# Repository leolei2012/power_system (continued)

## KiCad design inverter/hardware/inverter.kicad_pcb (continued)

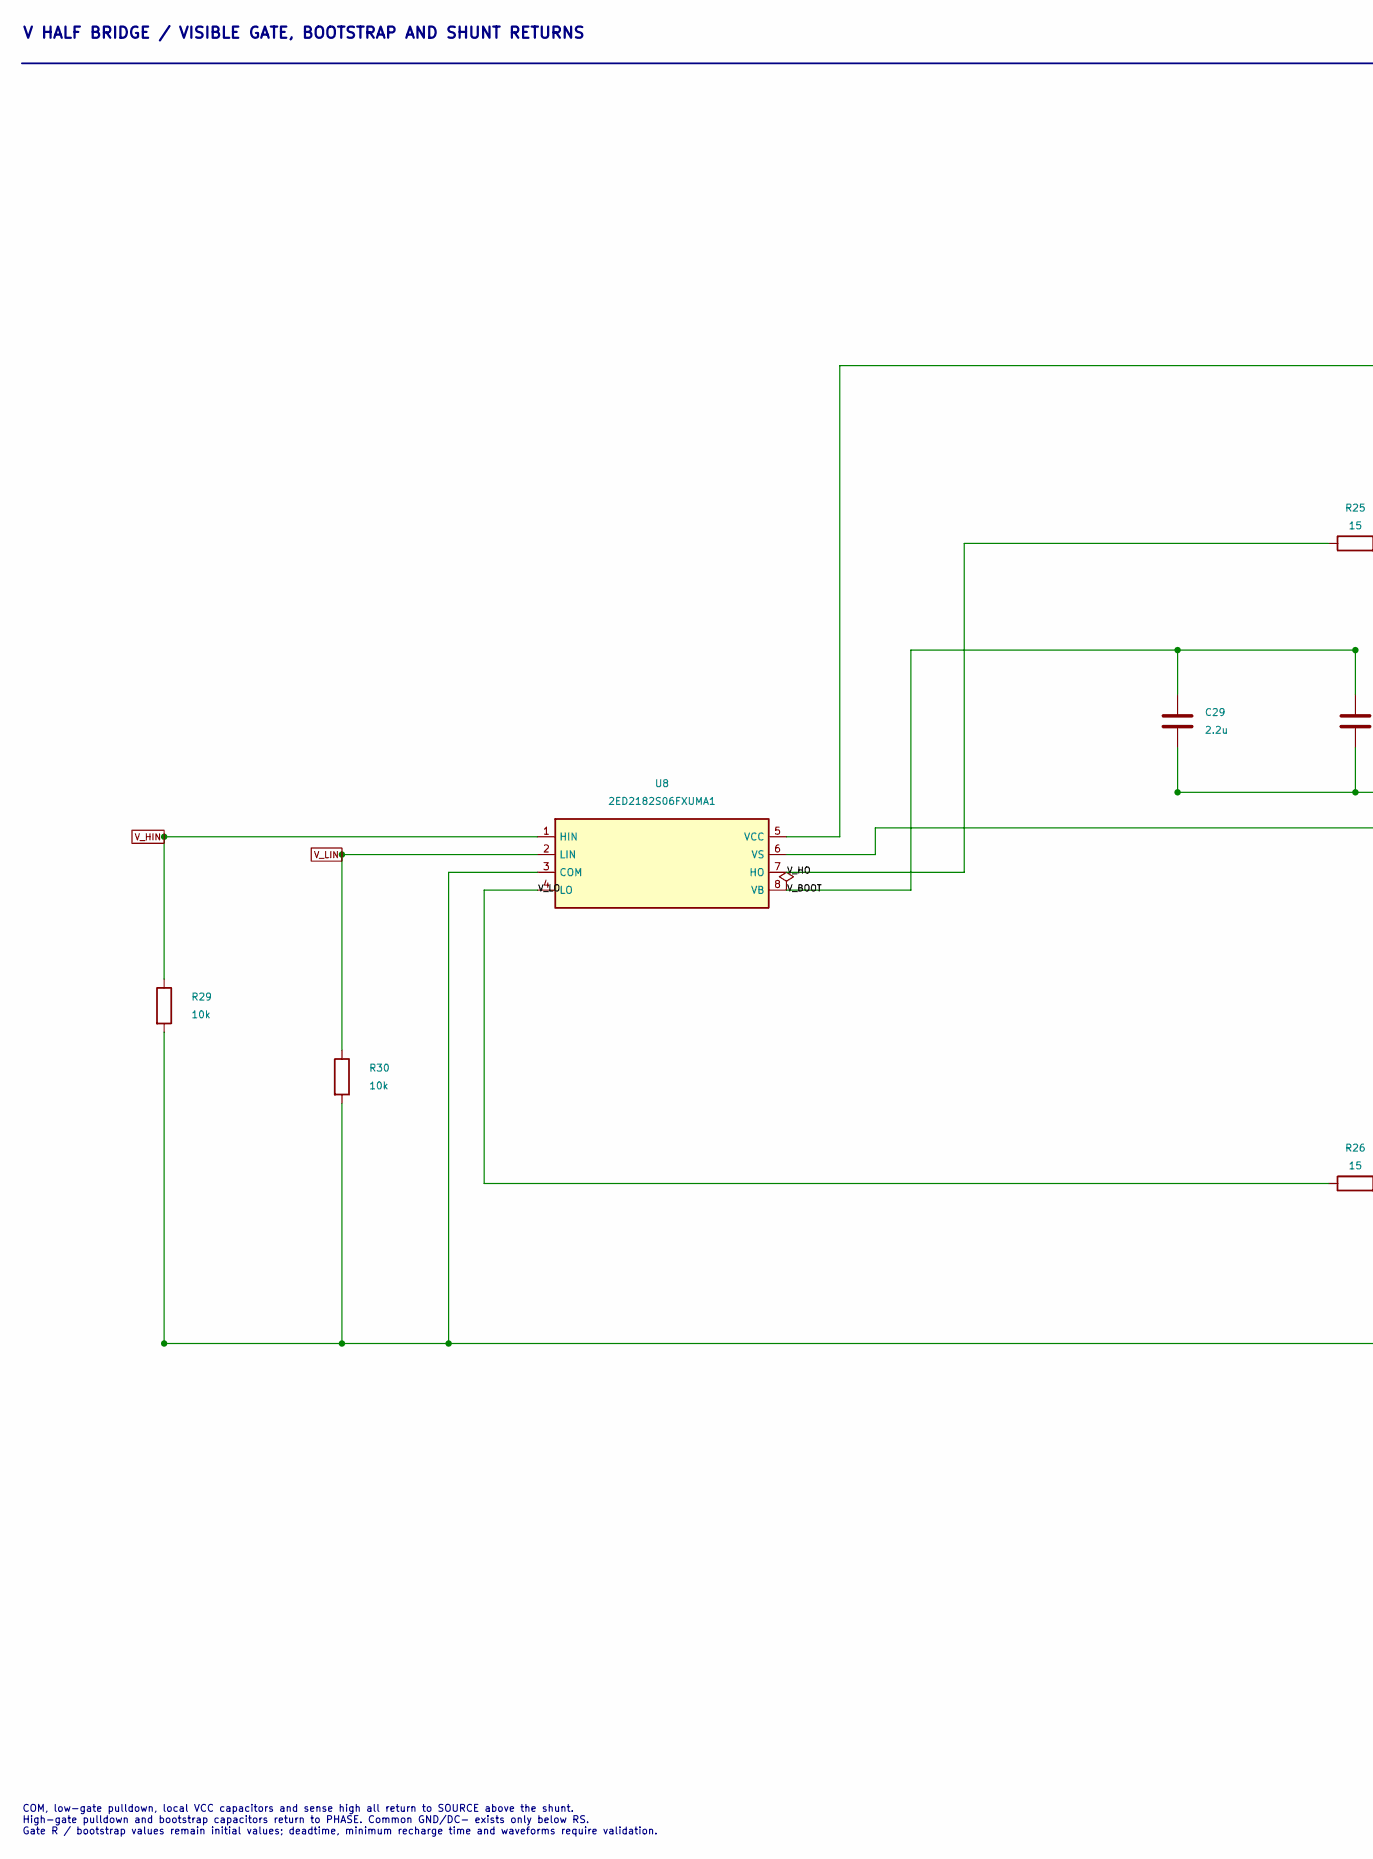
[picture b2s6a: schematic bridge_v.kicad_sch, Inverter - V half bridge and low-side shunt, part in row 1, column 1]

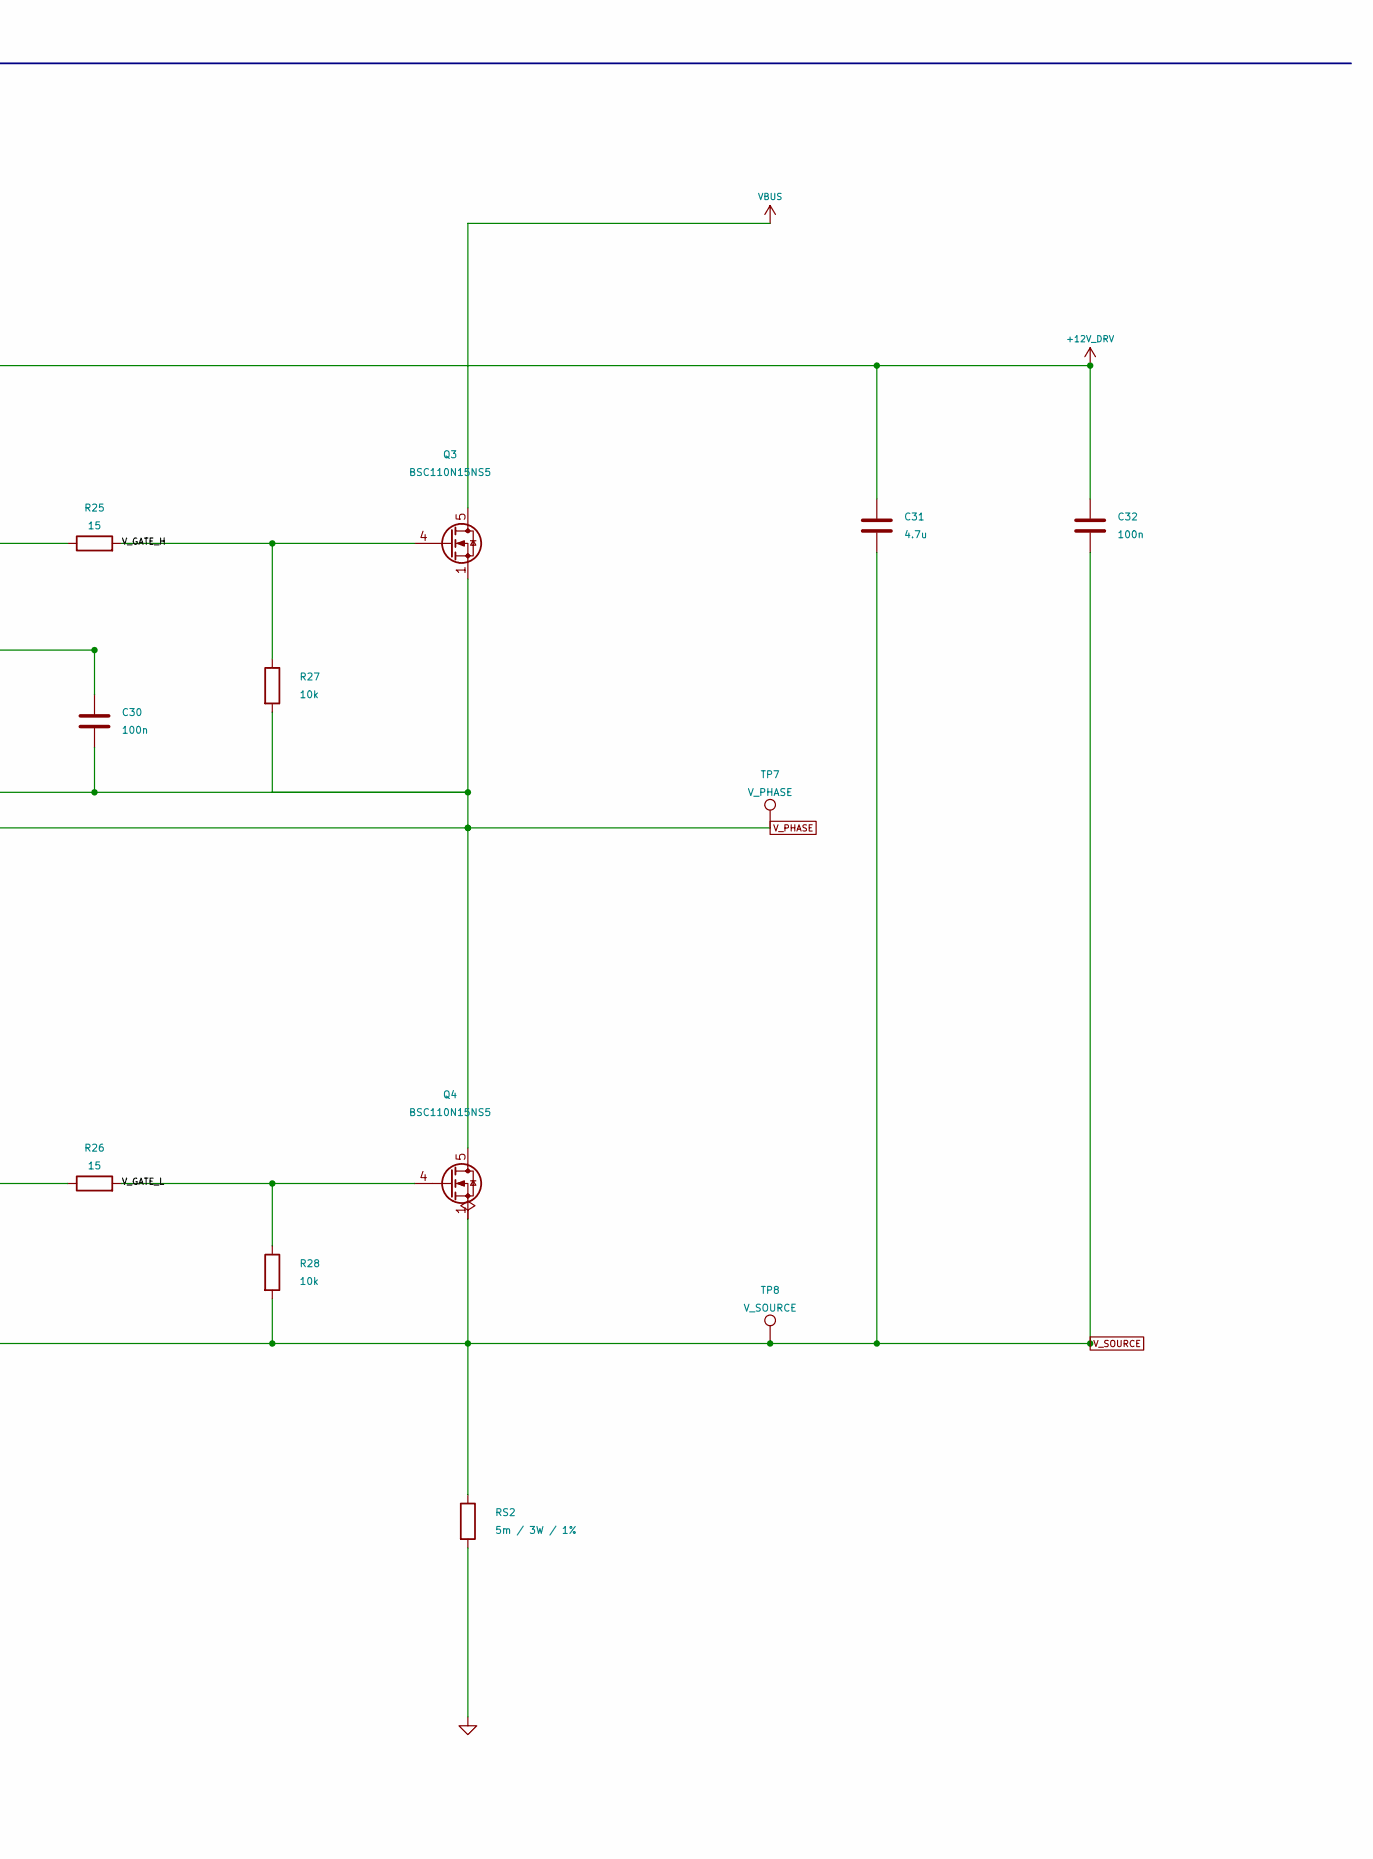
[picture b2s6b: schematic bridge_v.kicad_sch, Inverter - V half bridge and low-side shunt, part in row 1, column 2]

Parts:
C29: 2.2u; C_1206_3216Metric; Voltage_Rating 25V; MPN TBD
C30, C32: 100n; C_0603_1608Metric; Voltage_Rating 50V; Tolerance 10%; MPN CC0603KRX7R9BB104
C31: 4.7u; C_0805_2012Metric; Voltage_Rating 25V; MPN TBD
Q3, Q4: BSC110N15NS5; Infineon_BSC110N15NS5_PG-TDSON8_8PhysicalPins; MPN BSC110N15NS5ATMA1
R25, R26: 15; R_0805_2012Metric; Tolerance 1%; MPN TBD
R27, R28, R29, R30: 10k; R_0603_1608Metric; Tolerance 1%; MPN TBD
RS2: 5m / 3W / 1%; Milliohm_HoJLR2512_Pad2.1x4.0mm_Gap4.1mm; MPN HoJLR2512-3W-5mR-1%
TP7: V_PHASE; TestPoint_Pad_D1.5mm
TP8: V_SOURCE; TestPoint_Pad_D1.5mm
U8: 2ED2182S06FXUMA1; SOIC-8_3.9x4.9mm_P1.27mm; MPN 2ED2182S06FXUMA1

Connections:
+12V_DRV: C31.1, C32.1, U8.5 (VCC); also elsewhere on the board
/V half bridge/V_BOOT: C29.1, C30.1, U8.8 (VB)
/V half bridge/V_GATE_H: Q3.4 (G), R25.2, R27.1
/V half bridge/V_GATE_L: Q4.4 (G), R26.2, R28.1
/V half bridge/V_HO: R25.1, U8.7 (HO)
/V half bridge/V_LO: R26.1, U8.4 (LO)
VBUS: Q3.5 (D), Q3.6 (D), Q3.7 (D), Q3.8 (D); also elsewhere on the board
V_HIN: R29.1, U8.1 (HIN); also elsewhere on the board
V_LIN: R30.1, U8.2 (LIN); also elsewhere on the board
V_PHASE: C29.2, C30.2, Q3.1 (S), Q3.2 (S), Q3.3 (S), Q4.5 (D), Q4.6 (D), Q4.7 (D), Q4.8 (D), R27.2, TP7.1, U8.6 (VS); also elsewhere on the board
V_SOURCE: C31.2, C32.2, Q4.1 (S), Q4.2 (S), Q4.3 (S), R28.2, R29.2, R30.2, RS2.1, TP8.1, U8.3 (COM); also elsewhere on the board

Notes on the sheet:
V HALF BRIDGE / VISIBLE GATE, BOOTSTRAP AND SHUNT RETURNS
COM, low-gate pulldown, local VCC capacitors and sense high all return to SOURCE above the shunt. High-gate pulldown and bootstrap capacitors return to PHASE. Common GND/DC- exists only below RS. Gate R / bootstrap values remain initial values; deadtime, minimum recharge time and waveforms require 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

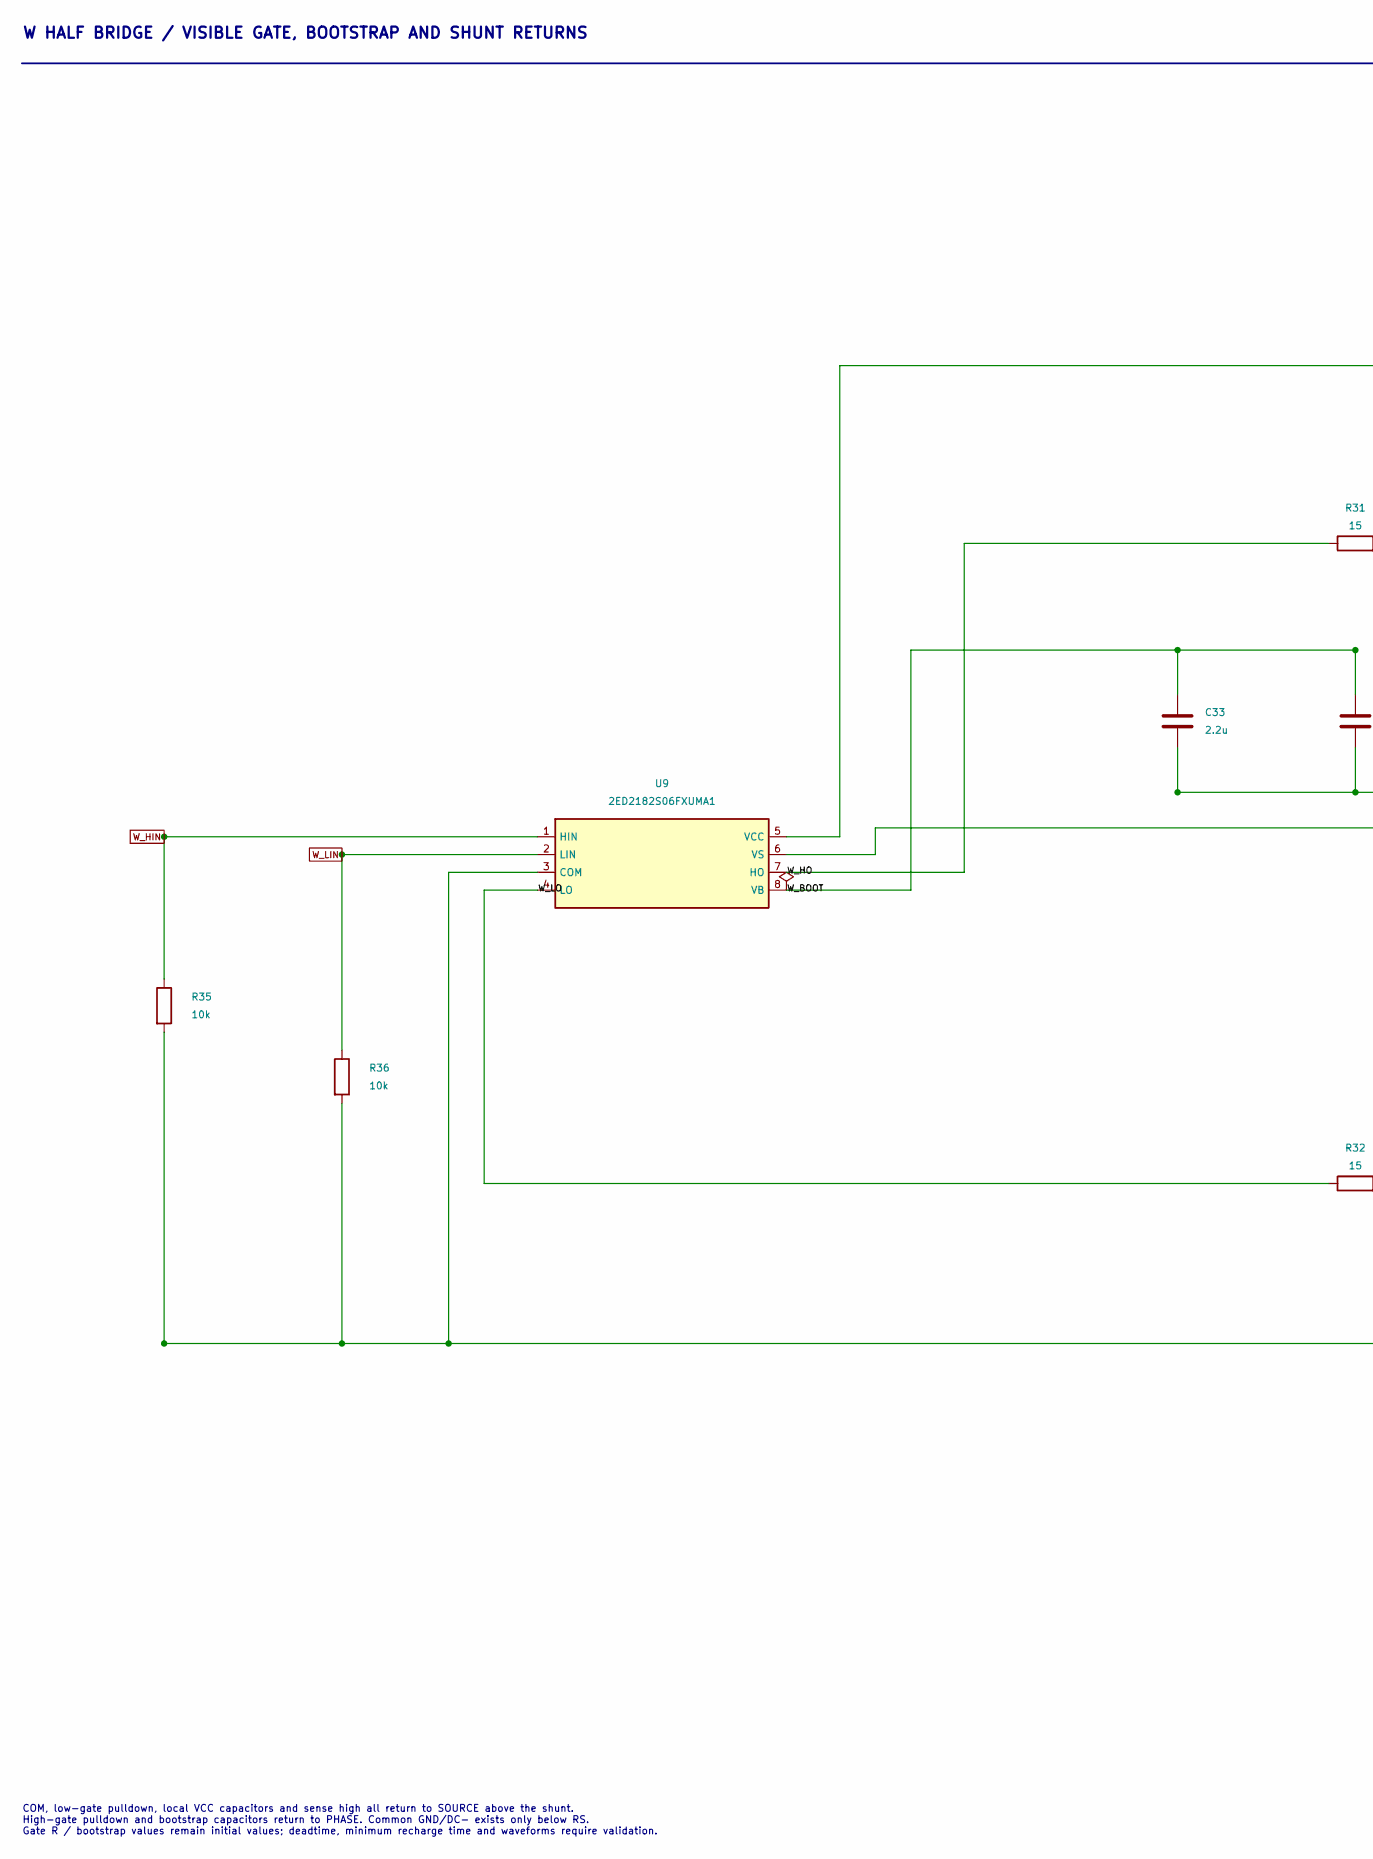
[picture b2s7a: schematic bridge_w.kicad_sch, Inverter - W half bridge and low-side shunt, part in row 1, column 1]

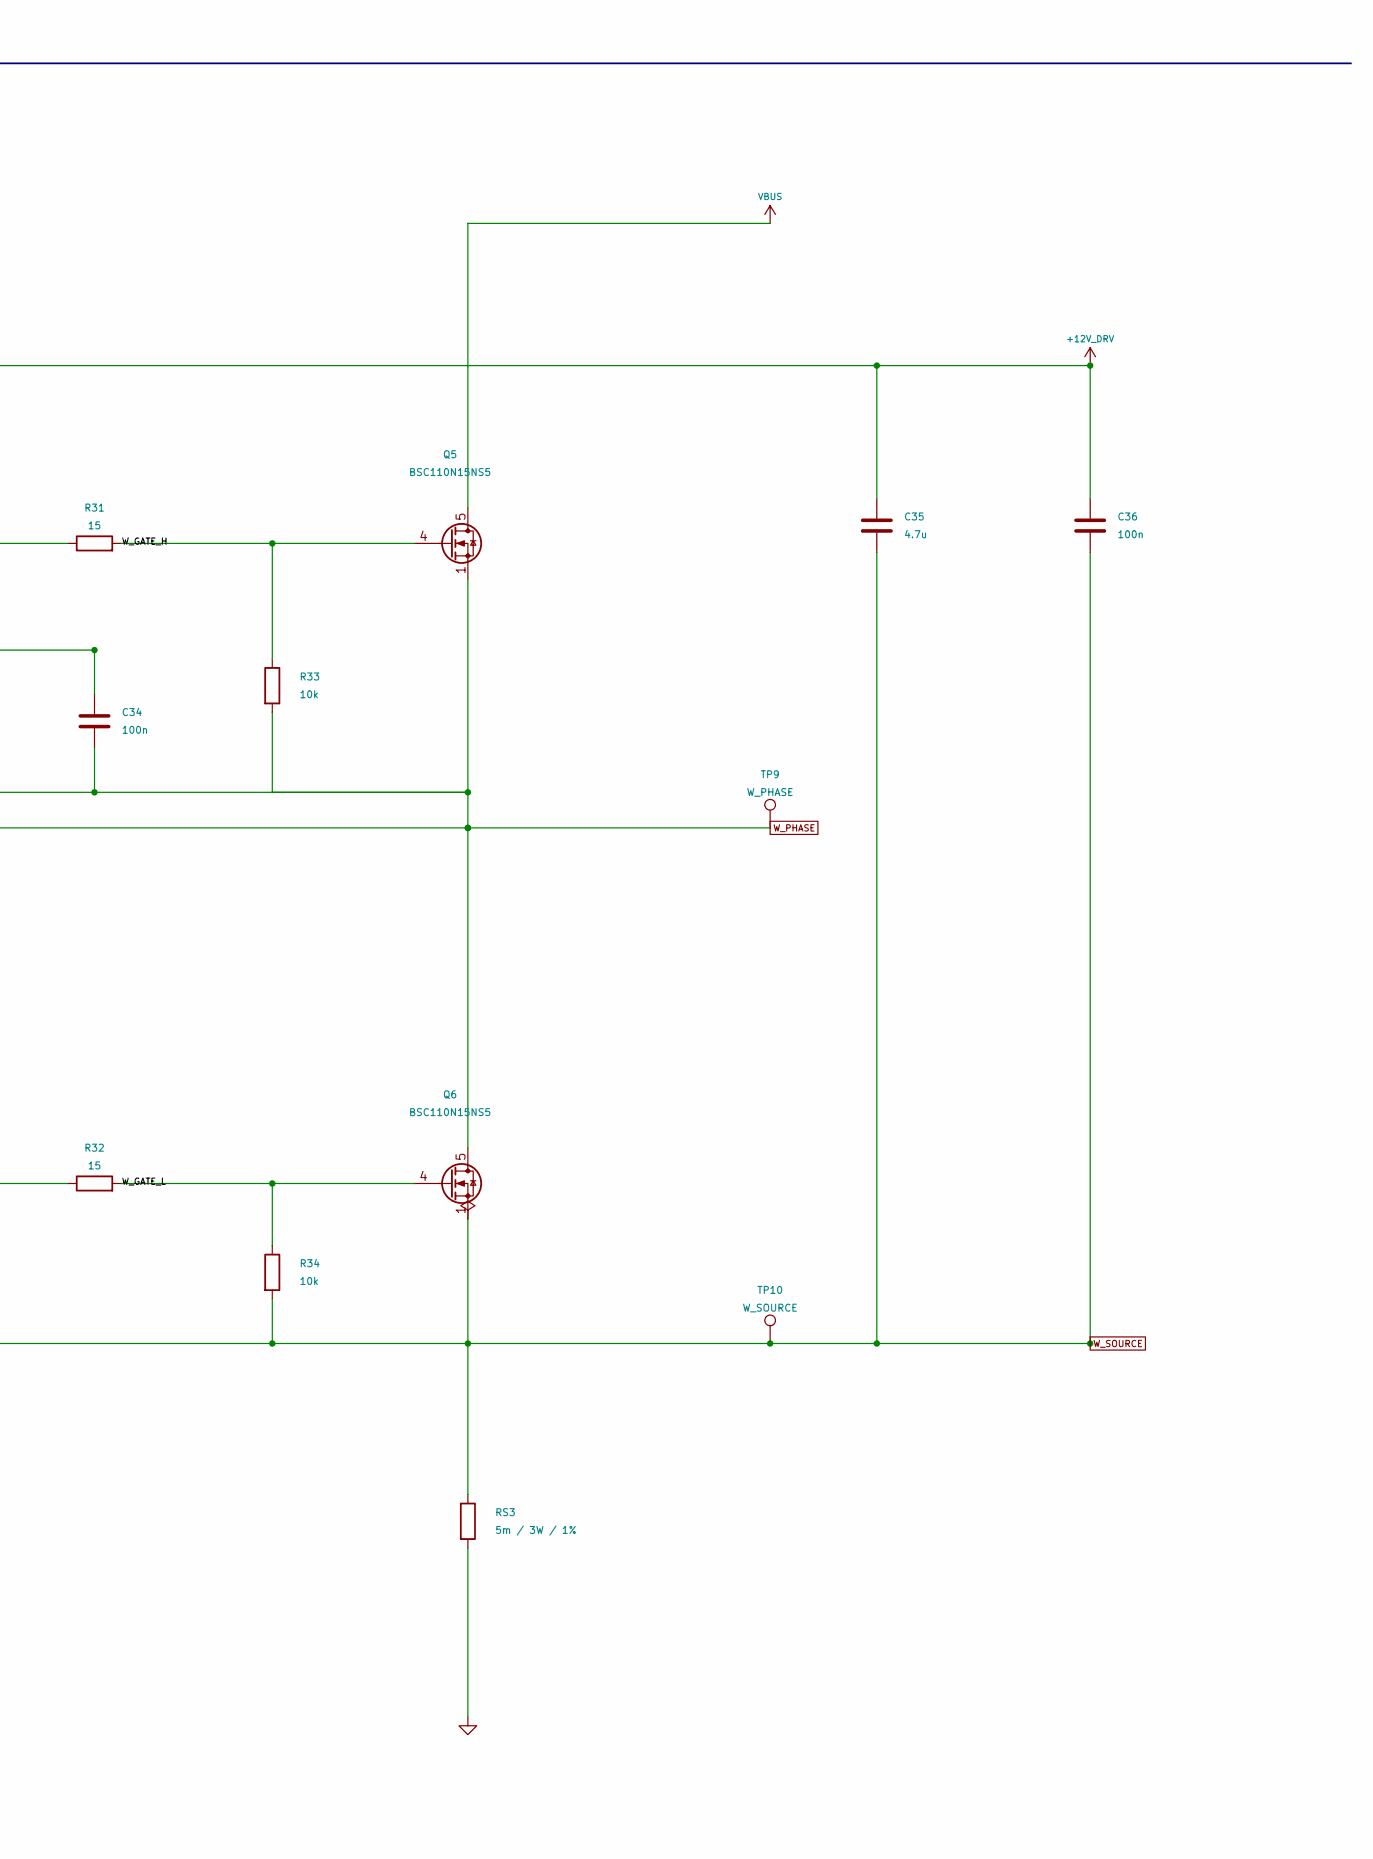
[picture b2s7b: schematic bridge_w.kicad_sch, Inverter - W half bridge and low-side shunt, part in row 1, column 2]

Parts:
C33: 2.2u; C_1206_3216Metric; Voltage_Rating 25V; MPN TBD
C34, C36: 100n; C_0603_1608Metric; Voltage_Rating 50V; Tolerance 10%; MPN CC0603KRX7R9BB104
C35: 4.7u; C_0805_2012Metric; Voltage_Rating 25V; MPN TBD
Q5, Q6: BSC110N15NS5; Infineon_BSC110N15NS5_PG-TDSON8_8PhysicalPins; MPN BSC110N15NS5ATMA1
R31, R32: 15; R_0805_2012Metric; Tolerance 1%; MPN TBD
R33, R34, R35, R36: 10k; R_0603_1608Metric; Tolerance 1%; MPN TBD
RS3: 5m / 3W / 1%; Milliohm_HoJLR2512_Pad2.1x4.0mm_Gap4.1mm; MPN HoJLR2512-3W-5mR-1%
TP9: W_PHASE; TestPoint_Pad_D1.5mm
TP10: W_SOURCE; TestPoint_Pad_D1.5mm
U9: 2ED2182S06FXUMA1; SOIC-8_3.9x4.9mm_P1.27mm; MPN 2ED2182S06FXUMA1

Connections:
+12V_DRV: C35.1, C36.1, U9.5 (VCC); also elsewhere on the board
/W half bridge/W_BOOT: C33.1, C34.1, U9.8 (VB)
/W half bridge/W_GATE_H: Q5.4 (G), R31.2, R33.1
/W half bridge/W_GATE_L: Q6.4 (G), R32.2, R34.1
/W half bridge/W_HO: R31.1, U9.7 (HO)
/W half bridge/W_LO: R32.1, U9.4 (LO)
VBUS: Q5.5 (D), Q5.6 (D), Q5.7 (D), Q5.8 (D); also elsewhere on the board
W_HIN: R35.1, U9.1 (HIN); also elsewhere on the board
W_LIN: R36.1, U9.2 (LIN); also elsewhere on the board
W_PHASE: C33.2, C34.2, Q5.1 (S), Q5.2 (S), Q5.3 (S), Q6.5 (D), Q6.6 (D), Q6.7 (D), Q6.8 (D), R33.2, TP9.1, U9.6 (VS); also elsewhere on the board
W_SOURCE: C35.2, C36.2, Q6.1 (S), Q6.2 (S), Q6.3 (S), R34.2, R35.2, R36.2, RS3.1, TP10.1, U9.3 (COM); also elsewhere on the board

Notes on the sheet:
W HALF BRIDGE / VISIBLE GATE, BOOTSTRAP AND SHUNT RETURNS
COM, low-gate pulldown, local VCC capacitors and sense high all return to SOURCE above the shunt. High-gate pulldown and bootstrap capacitors return to PHASE. Common GND/DC- exists only below RS. Gate R / bootstrap values remain initial values; deadtime, minimum recharge time and waveforms require 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

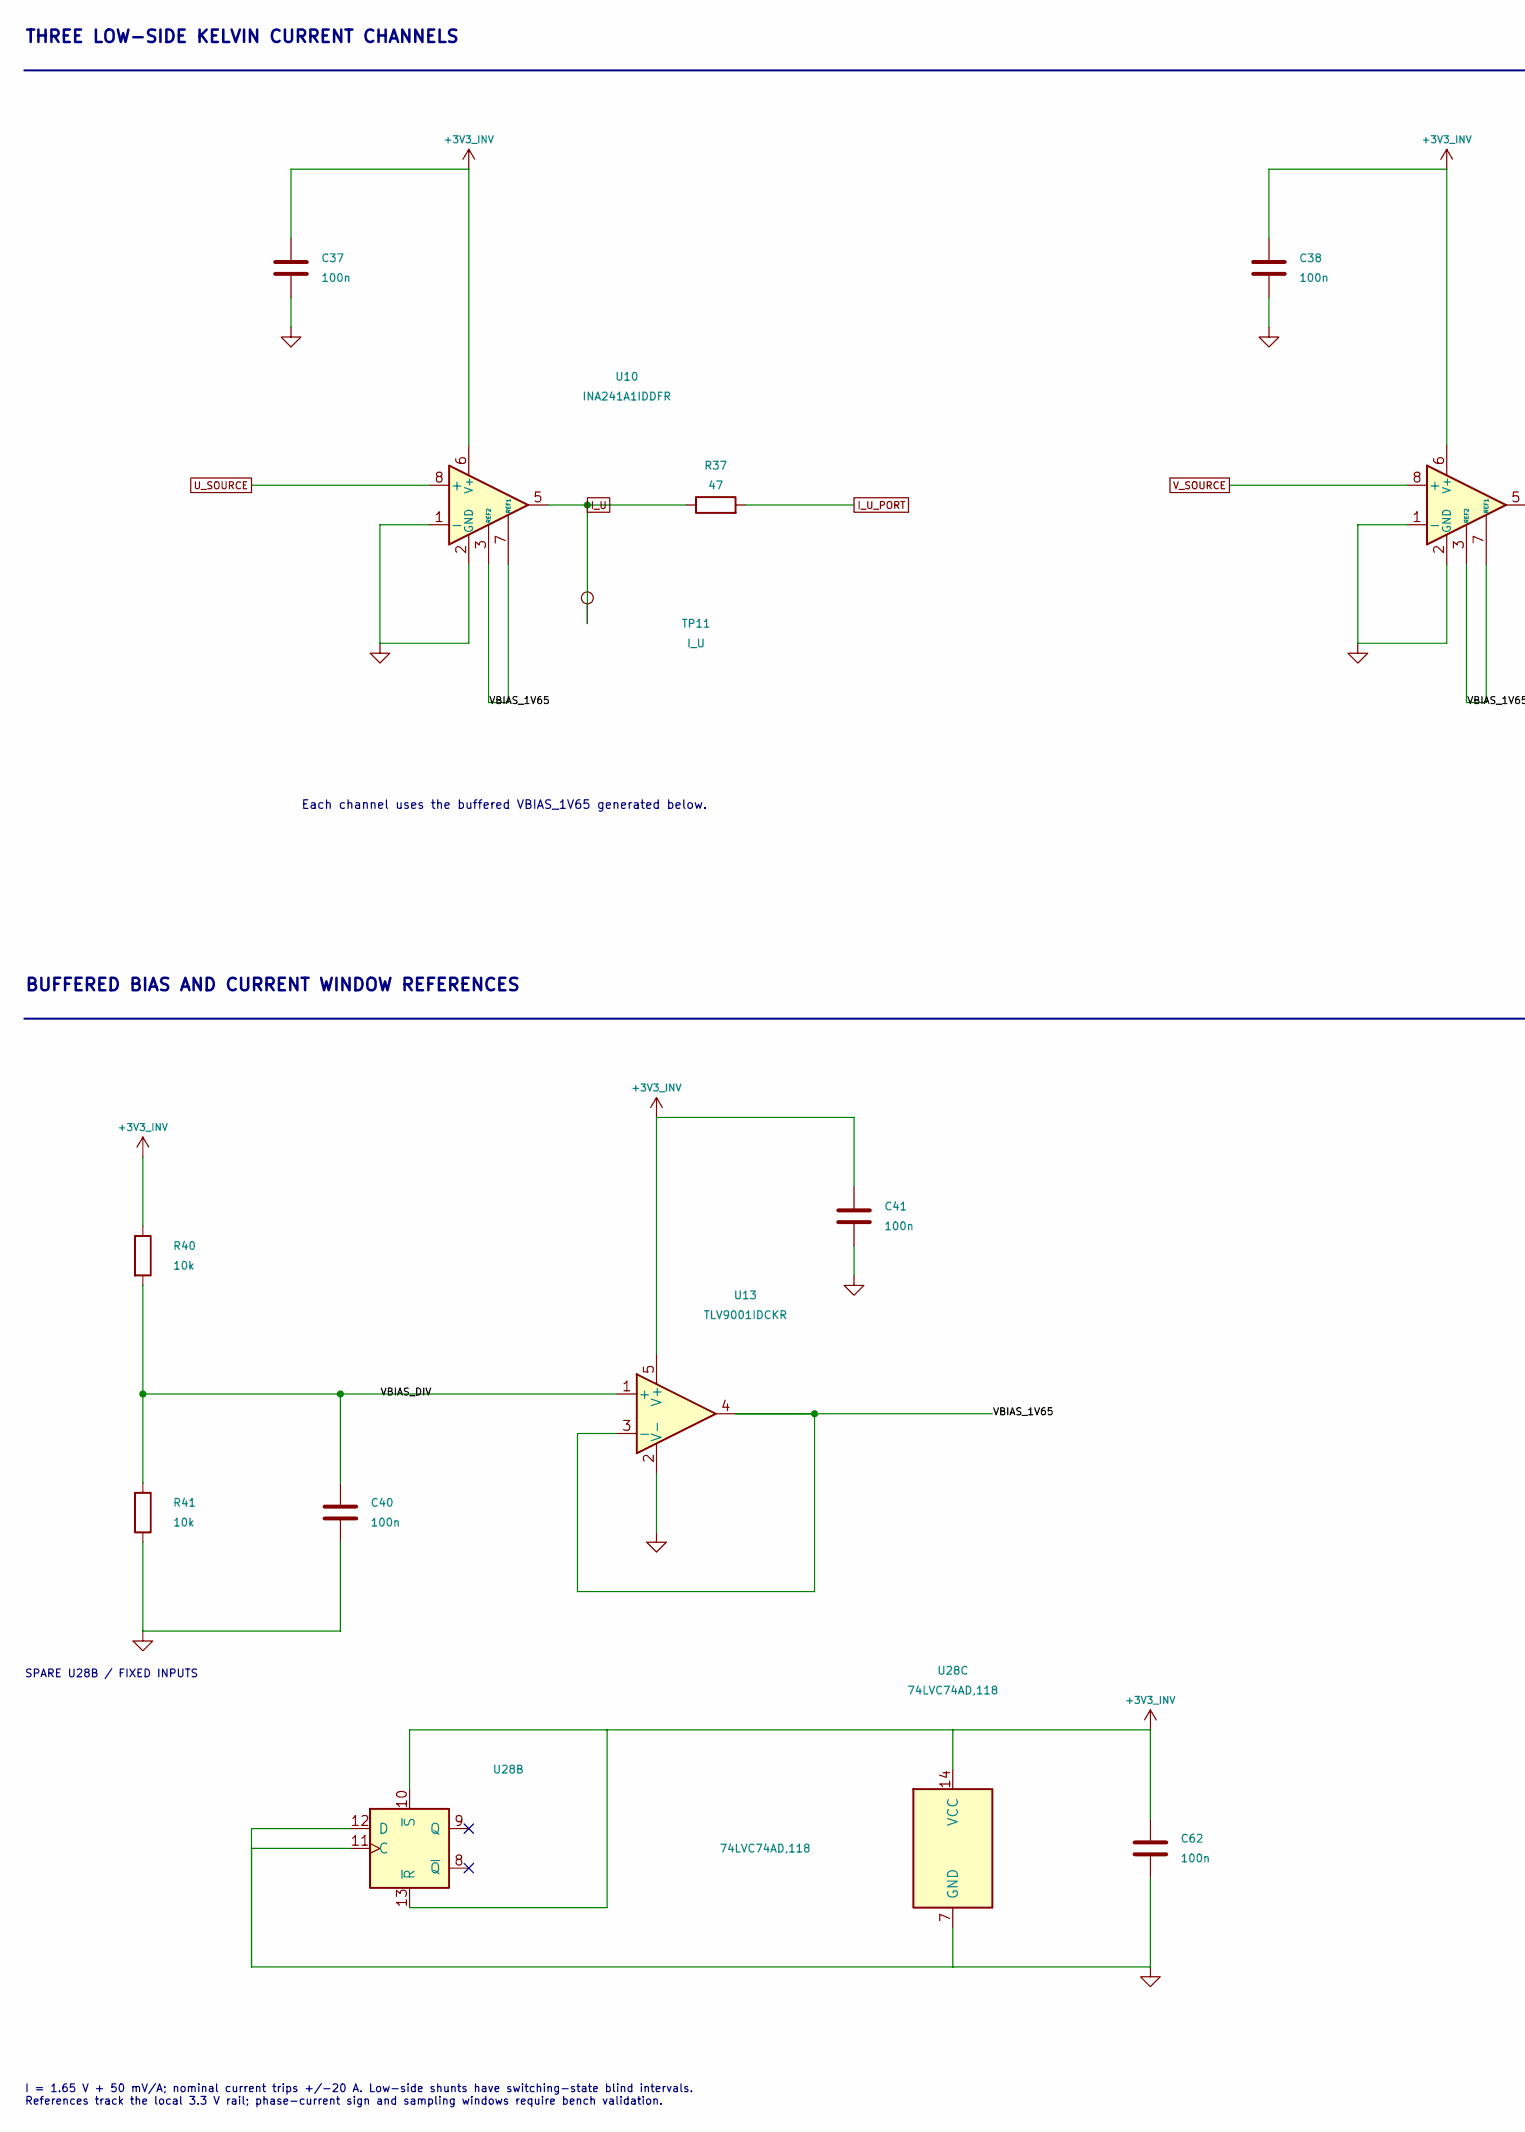
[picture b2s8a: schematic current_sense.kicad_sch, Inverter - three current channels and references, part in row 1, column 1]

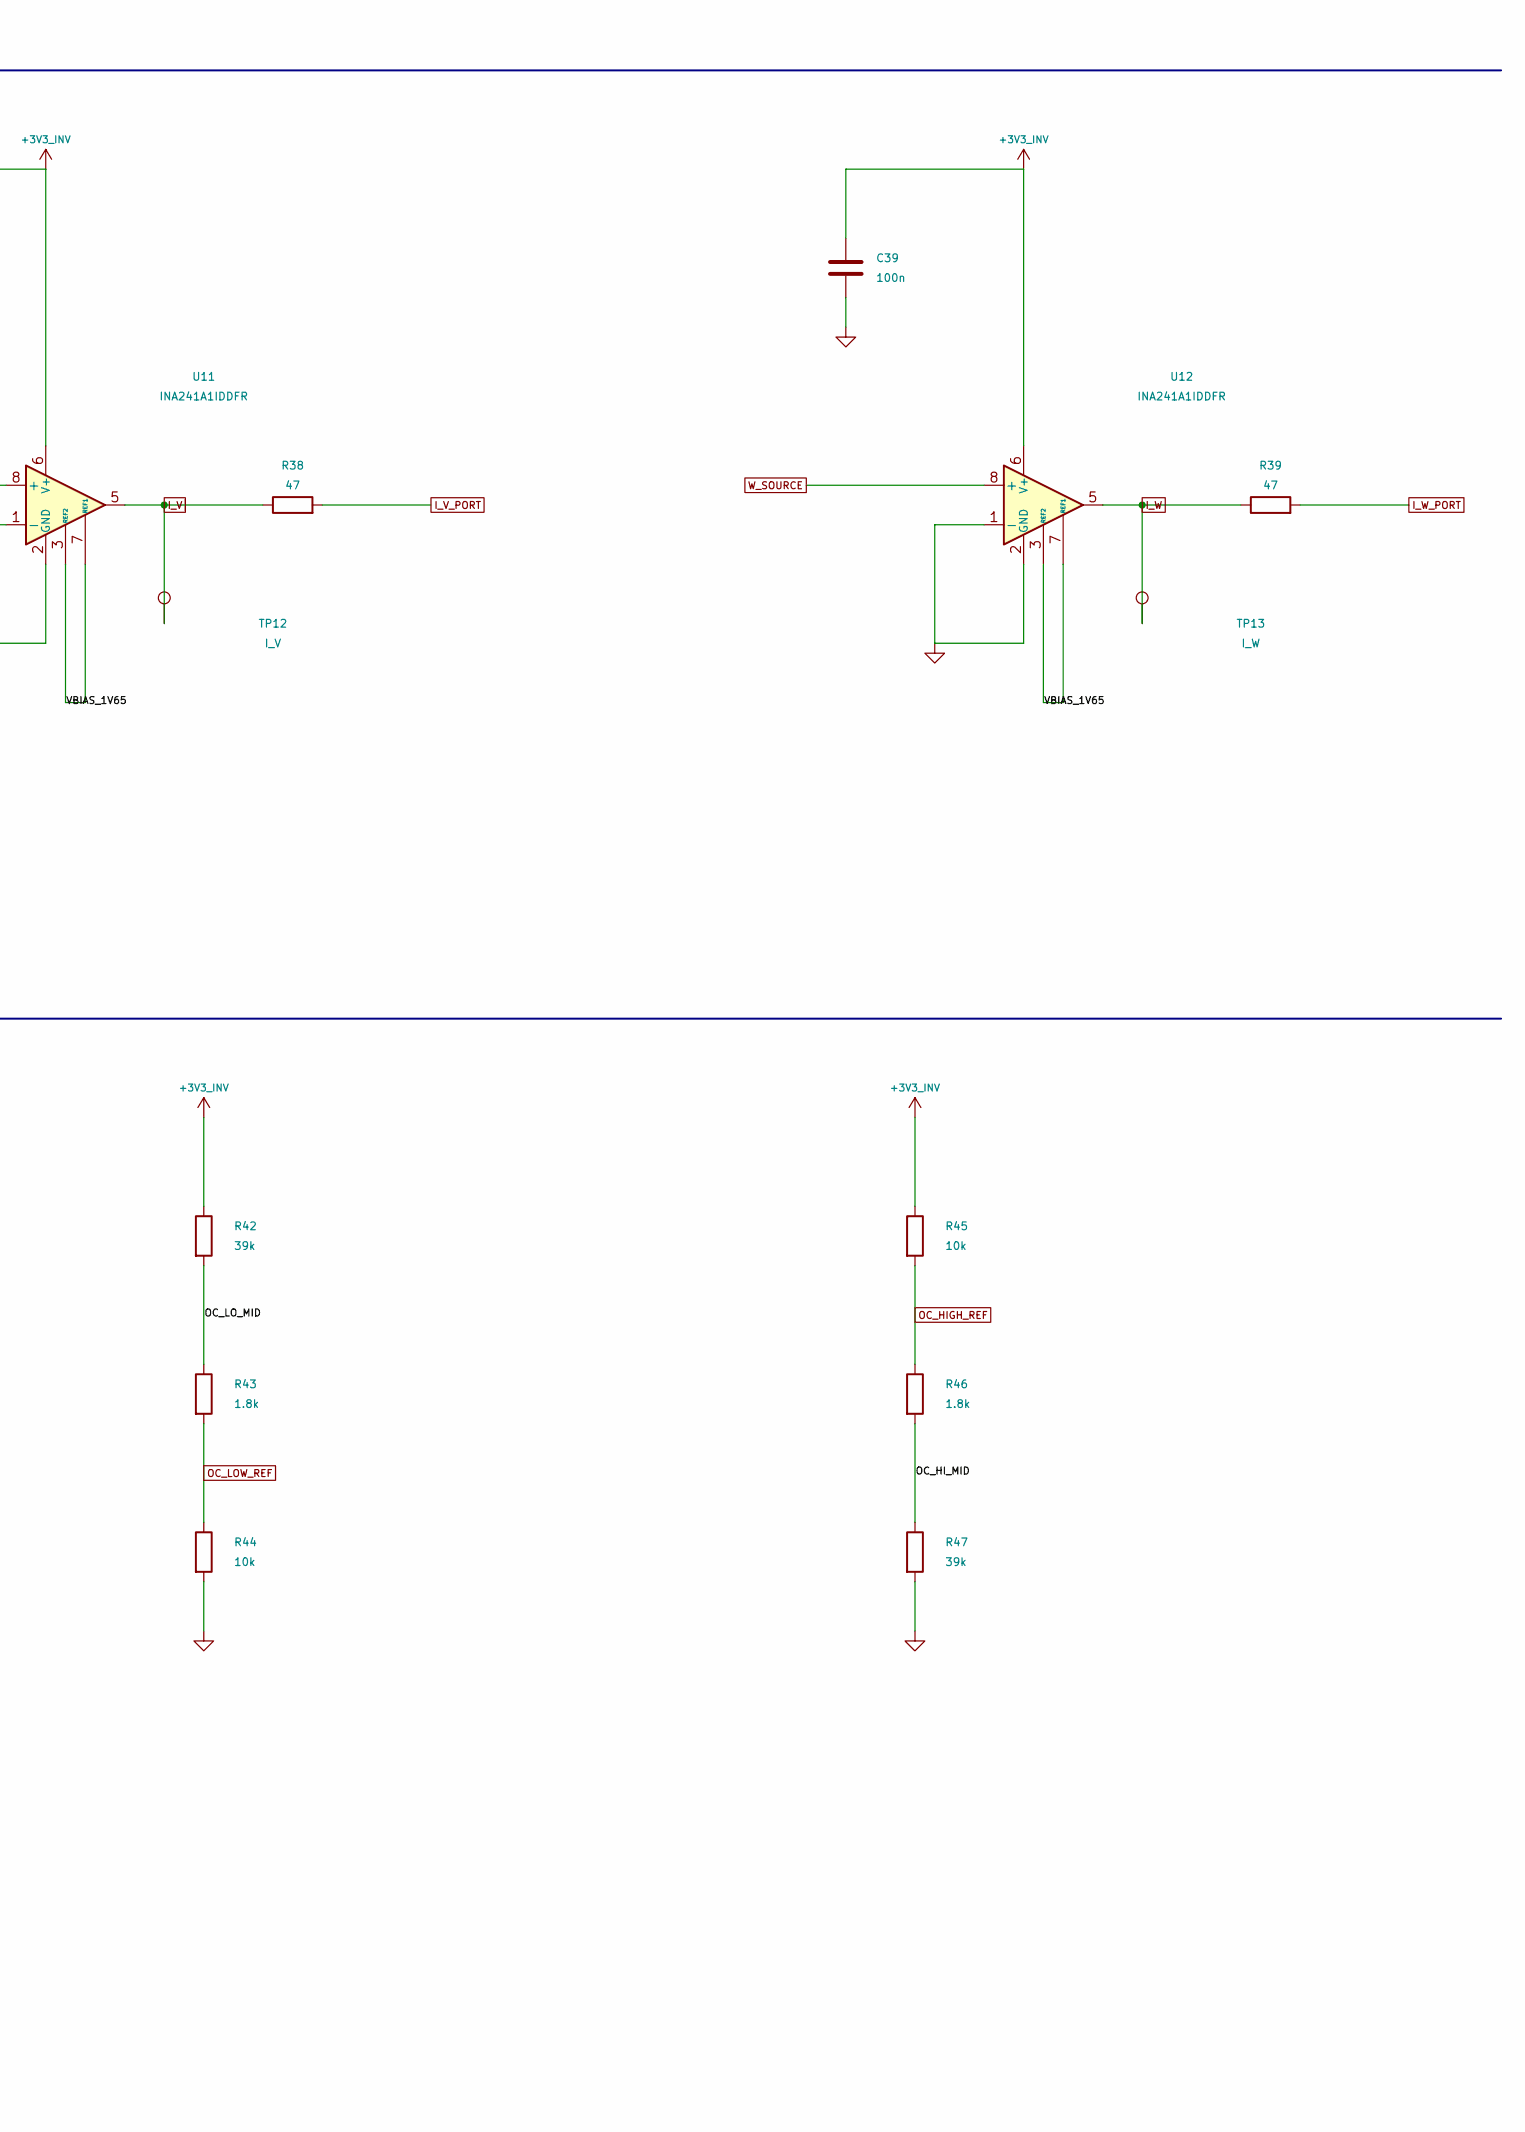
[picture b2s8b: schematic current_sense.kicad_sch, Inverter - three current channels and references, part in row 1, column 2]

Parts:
C37, C38, C39: 100n; C_0603_1608Metric; Voltage_Rating 50V; Tolerance 10%; MPN CC0603KRX7R9BB104
C40, C41, C62: 100n; C_0402_1005Metric; Voltage_Rating 25V; MPN TBD
R37, R38, R39: 47; R_0603_1608Metric; Tolerance 1%; MPN TBD
R40, R41, R44, R45: 10k; R_0402_1005Metric; Tolerance 0.1%; MPN TBD
R42, R47: 39k; R_0402_1005Metric; Tolerance 0.1%; MPN TBD
R43, R46: 1.8k; R_0402_1005Metric; Tolerance 0.1%; MPN TBD
TP11: I_U; TestPoint_Pad_D1.5mm
TP12: I_V; TestPoint_Pad_D1.5mm
TP13: I_W; TestPoint_Pad_D1.5mm
U10, U11, U12: INA241A1IDDFR; SOT-23-8; MPN INA241A1IDDFR
U13: TLV9001IDCKR; SOT-353_SC-70-5; MPN TLV9001IDCKR
U28: 74LVC74AD,118; SOIC-14_3.9x8.7mm_P1.27mm; MPN 74LVC74AD,118

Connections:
+3V3_INV: C37.1, C38.1, C39.1, C41.1, C62.1, R40.1, R42.1, R45.1, U10.6 (V+), U11.6 (V+), U12.6 (V+), U13.5 (V+), U28.10 (~S), U28.13 (~R), U28.14 (VCC); also elsewhere on the board
/Current sensing/OC_HI_MID: R46.2, R47.1
/Current sensing/OC_LO_MID: R42.2, R43.1
/Current sensing/VBIAS_1V65: U10.3 (REF2), U10.7 (REF1), U11.3 (REF2), U11.7 (REF1), U12.3 (REF2), U12.7 (REF1), U13.3 (-), U13.4
/Current sensing/VBIAS_DIV: C40.1, R40.2, R41.1, U13.1 (+)
I_U: R37.1, TP11.1, U10.5; also elsewhere on the board
I_U_PORT: R37.2; also elsewhere on the board
I_V: R38.1, TP12.1, U11.5; also elsewhere on the board
I_V_PORT: R38.2; also elsewhere on the board
I_W: R39.1, TP13.1, U12.5; also elsewhere on the board
I_W_PORT: R39.2; also elsewhere on the board
OC_HIGH_REF: R45.2, R46.1; also elsewhere on the board
OC_LOW_REF: R43.2, R44.1; also elsewhere on the board
U_SOURCE: U10.8 (+); also elsewhere on the board
V_SOURCE: U11.8 (+); also elsewhere on the board
W_SOURCE: U12.8 (+); also elsewhere on the board

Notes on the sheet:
THREE LOW-SIDE KELVIN CURRENT CHANNELS
Each channel uses the buffered VBIAS_1V65 generated below.
BUFFERED BIAS AND CURRENT WINDOW REFERENCES
SPARE U28B / FIXED INPUTS
I = 1.65 V + 50 mV/A; nominal current trips +/-20 A. Low-side shunts have switching-state blind intervals. References track the local 3.3 V rail; phase-current sign and sampling windows require bench validation.

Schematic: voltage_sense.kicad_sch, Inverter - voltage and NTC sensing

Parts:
C42: 100p; C_0402_1005Metric; Voltage_Rating 25V; MPN TBD
C43, C45, C47, C49: 100n; C_0402_1005Metric; Voltage_Rating 25V; MPN TBD
C44, C46, C48: 1n; C_0402_1005Metric; Voltage_Rating 25V; MPN TBD
C50: 10n; C_0402_1005Metric; Voltage_Rating 25V; MPN TBD
J8: EXTERNAL 10k NTC; HCTL_PZ127_1x02_P1.27mm_Drill0.70mm; MPN PZ127-1-02-Z
R48, R49, R53, R54, R58, R59, R63, R64: 240k; R_0805_2012Metric; Tolerance 0.1%; MPN TBD
R50, R51, R55, R56, R60, R61, R65, R66: 10k; R_0603_1608Metric; Tolerance 0.1%; MPN TBD
R52, R57, R62, R67: 47; R_0402_1005Metric; Tolerance 1%; MPN TBD
R68: 20k; R_0402_1005Metric; Tolerance 0.1%; MPN TBD
R69: 13k; R_0402_1005Metric; Tolerance 0.1%; MPN TBD
R70: 10k; R_0402_1005Metric; Tolerance 1%; MPN TBD
U14, U15, U16, U17: TLV9001IDCKR; SOT-353_SC-70-5; MPN TLV9001IDCKR

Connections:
+3V3_INV: C43.1, C45.1, C47.1, C49.1, R68.1, R70.1, U14.5 (V+), U15.5 (V+), U16.5 (V+), U17.5 (V+); also elsewhere on the board
/Voltage and NTC/V_DC_DIV: C42.1, R50.2, R51.1, U14.1 (+)
/Voltage and NTC/V_DC_DIV1: R48.2, R49.1
/Voltage and NTC/V_DC_DIV2: R49.2, R50.1
/Voltage and NTC/V_U: R57.1, U15.3 (-), U15.4
/Voltage and NTC/V_U_DIV: C44.1, R55.2, R56.1, U15.1 (+)
/Voltage and NTC/V_U_DIV1: R53.2, R54.1
/Voltage and NTC/V_U_DIV2: R54.2, R55.1
/Voltage and NTC/V_V: R62.1, U16.3 (-), U16.4
/Voltage and NTC/V_V_DIV: C46.1, R60.2, R61.1, U16.1 (+)
/Voltage and NTC/V_V_DIV1: R58.2, R59.1
/Voltage and NTC/V_V_DIV2: R59.2, R60.1
/Voltage and NTC/V_W: R67.1, U17.3 (-), U17.4
/Voltage and NTC/V_W_DIV: C48.1, R65.2, R66.1, U17.1 (+)
/Voltage and NTC/V_W_DIV1: R63.2, R64.1
/Voltage and NTC/V_W_DIV2: R64.2, R65.1
OV_REF_1V30: R68.2, R69.1; also elsewhere on the board
TEMP_NTC: C50.1, J8.1, R70.2; also elsewhere on the board
U_PHASE: R53.1; also elsewhere on the board
VBUS: R48.1; also elsewhere on the board
V_DC: R52.1, U14.3 (-), U14.4; also elsewhere on the board
V_DC_PORT: R52.2; also elsewhere on the board
V_PHASE: R58.1; also elsewhere on the board
V_U_PORT: R57.2; also elsewhere on the board
V_V_PORT: R62.2; also elsewhere on the board
V_W_PORT: R67.2; also elsewhere on the board
W_PHASE: R63.1; also elsewhere on the board

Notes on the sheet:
FOUR 50:1 VOLTAGE CHANNELS / COMPLETE DIVIDER TO BUFFER
BUS OVERVOLTAGE REFERENCE / EXTERNAL NTC
20k / 13k gives 1.30 V 65 V nominal bus trip at 50:1.
Raw phase sense is measured before an external LC filter. Bus RC ~0.98 us; phase RC ~9.8 us. External NTC nominal 10k; beta, physical placement and cable protection remain to be selected.

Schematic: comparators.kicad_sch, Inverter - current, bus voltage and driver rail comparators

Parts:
C51, C52, C53: 100n; C_0603_1608Metric; Voltage_Rating 50V; Tolerance 10%; MPN CC0603KRX7R9BB104
C54: 100n; C_0402_1005Metric; Voltage_Rating 25V; MPN TBD
R71: 76.1k; R_0402_1005Metric; Tolerance 0.1%; MPN TBD
R72: 10k; R_0402_1005Metric; Tolerance 0.1%; MPN TBD
U18, U19, U20, U21: TLV3202AIDGK; VSSOP-8_3x3mm_P0.65mm; MPN TLV3202AIDGK

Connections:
+3V3_INV: C51.1, C52.1, C53.1, C54.1, U18.8 (V+), U19.8 (V+), U20.8 (V+), U21.8 (V+); also elsewhere on the board
+12V_DRV: R71.1; also elsewhere on the board
/Analog protection/DRV_UV_DIV: R71.2, R72.1, U21.5 (+)
BUS_OV_OK: U21.1; also elsewhere on the board
DRV_UV_OK: U21.7; also elsewhere on the board
I_U: U18.2 (-), U18.5 (+); also elsewhere on the board
I_V: U19.2 (-), U19.5 (+); also elsewhere on the board
I_W: U20.2 (-), U20.5 (+); also elsewhere on the board
OC_HIGH_REF: U18.3 (+), U19.3 (+), U20.3 (+); also elsewhere on the board
OC_LOW_REF: U18.6 (-), U19.6 (-), U20.6 (-); also elsewhere on the board
OC_U_HIGH_OK: U18.1; also elsewhere on the board
OC_U_LOW_OK: U18.7; also elsewhere on the board
OC_V_HIGH_OK: U19.1; also elsewhere on the board
OC_V_LOW_OK: U19.7; also elsewhere on the board
OC_W_HIGH_OK: U20.1; also elsewhere on the board
OC_W_LOW_OK: U20.7; also elsewhere on the board
OV_REF_1V30: U21.3 (+), U21.6 (-); also elsewhere on the board
V_DC: U21.2 (-); also elsewhere on the board

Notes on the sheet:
HARDWARE WINDOWS / EACH OUTPUT IS HEALTHY HIGH
BUS OVERVOLTAGE / DRIVER RAIL UNDERVOLTAGE
Healthy = HIGH. Window violation, bus >~65 V or driver rail <~11.193 V drives its own output LOW. Push-pull outputs enter separate AND inputs. No wired-AND; no intentional hysteresis; first event is latched.
